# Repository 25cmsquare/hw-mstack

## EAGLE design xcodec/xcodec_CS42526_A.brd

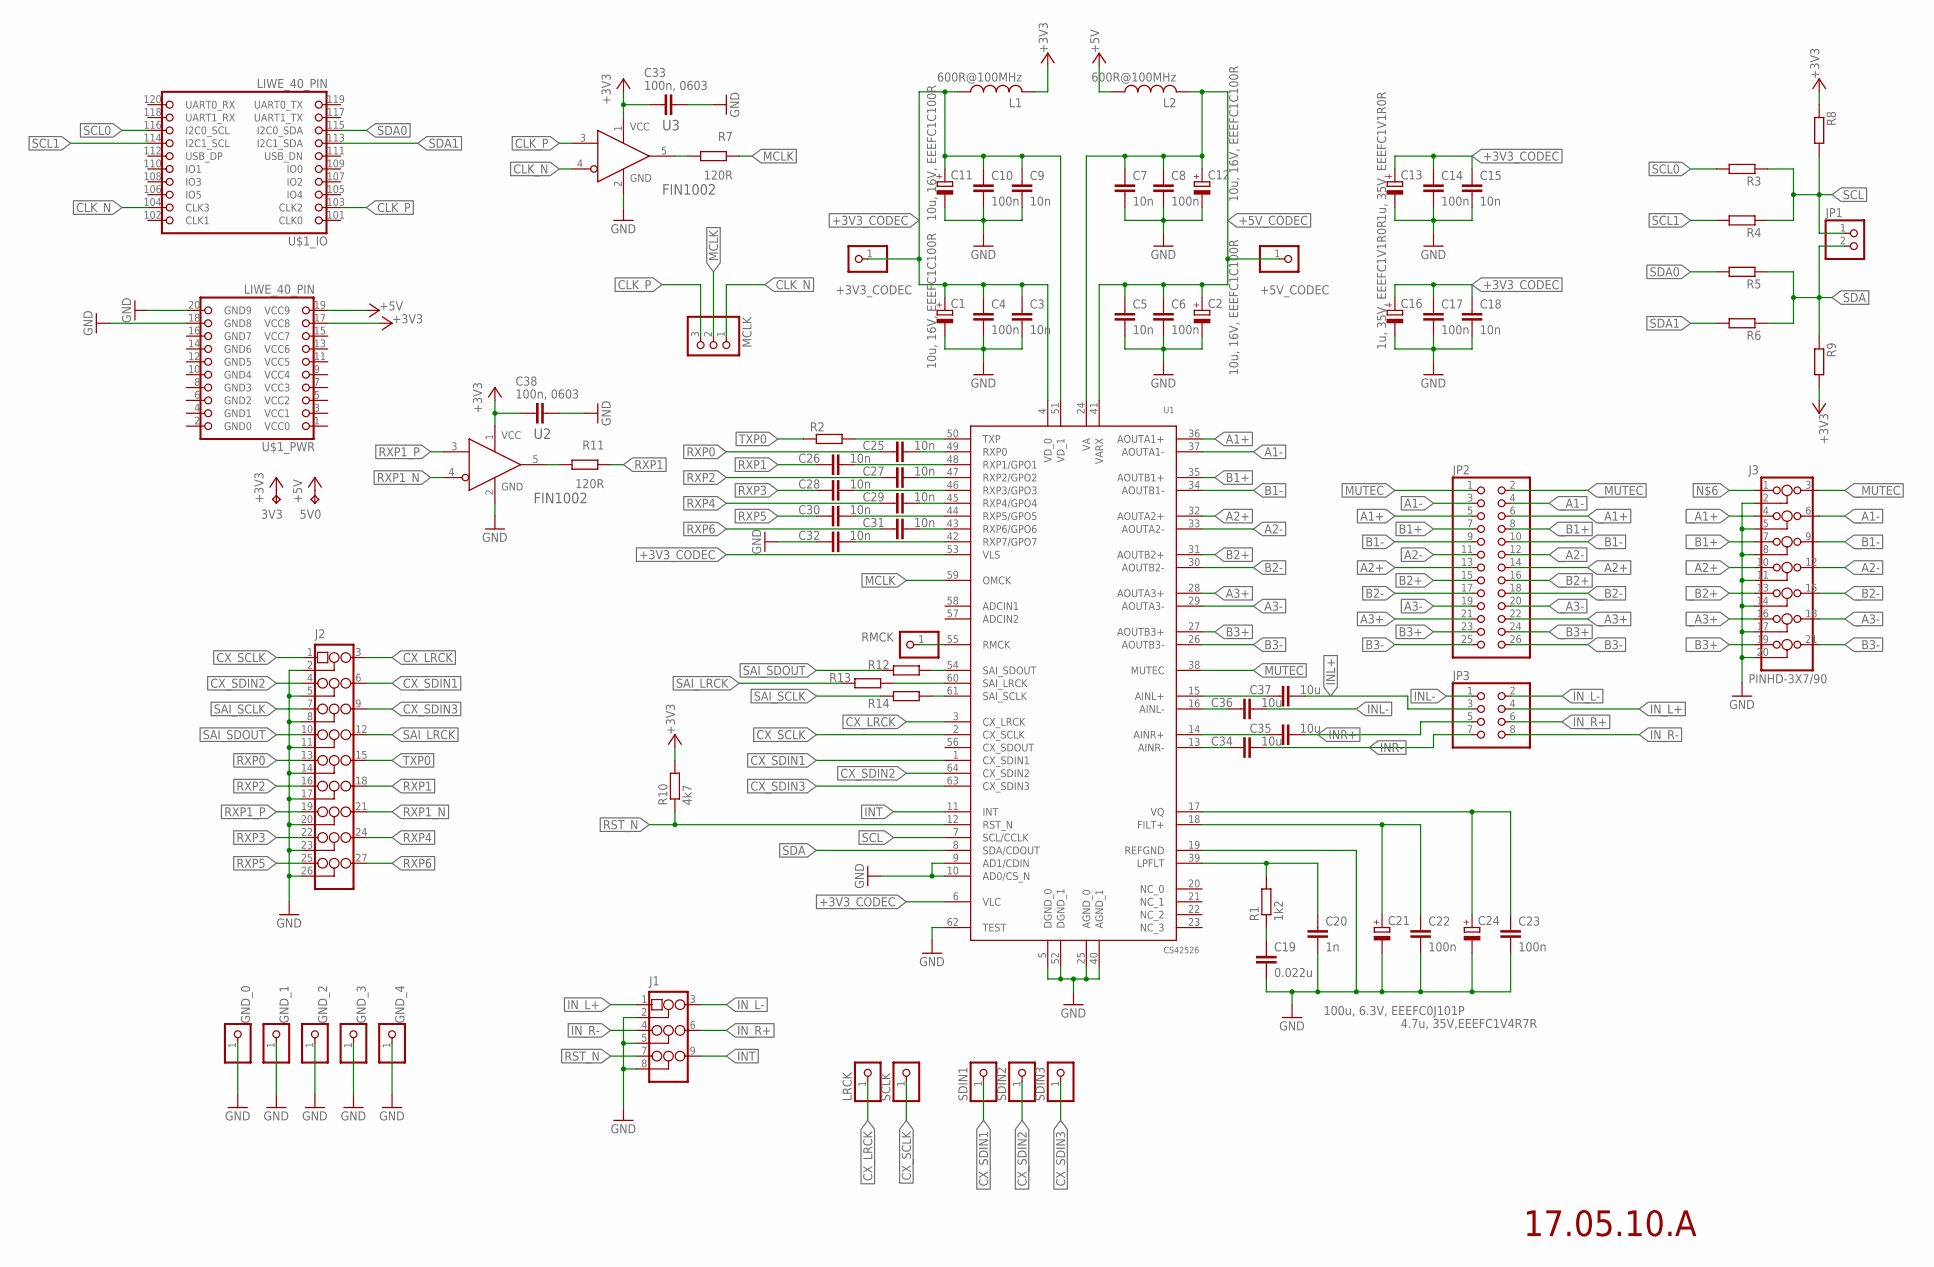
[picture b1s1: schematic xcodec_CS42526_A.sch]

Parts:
3V3, 5V0: TPTP14R; TP14R
+3V3_CODEC, +5V_CODEC: PINHD-1X1; 1X01
C1, C2, C11, C12: 10u, 16V, EEEFC1C100R; EEE-FC1V1R0AR
C3, C5, C7, C9, C15, C18, C25, C26, C27, C28, C29, C30, C31, C32: 10n; C0603K
C4, C6, C8, C10, C14, C17, C22, C23: 100n; C0603K
C13, C16: 1u, 35V, EEEFC1V1R0R; EEE-FC1V1R0AR
C19: 0.022u; C0603K
C20: 1n; C0603K
C21: 100u, 6.3V, EEEFC0J101P; EEE-FC1V220P
C24: 4.7u, 35V,EEEFC1V4R7R; EEE-FC1V1R0AR
C33, C38: 100n, 0603; C0603K
C34, C35, C36, C37: 10u; C0603K
GND_0, GND_1, GND_2, GND_3, GND_4: PINHD-1X1; 1X01
J1: PINHD-3X3/90; 3X03/90
J2: PINHD-3X9/90; 3X9/90
J3: PINHD-3X7/90; 3X07/90
JP1: PINHD-1X2; 1X02
JP2: PINHD-2X13; 2X13
JP3: PINHD-2X4; 2X04
L1, L2: 600R@100MHz; L0603
LRCK: PINHD-1X1; 1X01
MCLK: PINHD-1X3; 1X03
R1: 1k2; R0603
R2, R3, R4, R5, R6, R8, R9, R12, R13, R14: R-EU_R0603; R0603
R7, R11: 120R; R0603
R10: 4k7; R0603
RMCK: PINHD-1X1; 1X01
SCLK: PINHD-1X1; 1X01
SDIN1, SDIN2, SDIN3: PINHD-1X1; 1X01
U1: CS42526; LQFP_64
U2, U3: FIN1002; SOT95P280X140-5N
U$1: LIWE_40_PIN; LIWE_40_PIN_8X8

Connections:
+3V3: 3V3.TP, C33.2, C38.2, L1.2, R8.1, R9.2, R10.2, U2.1 (VCC), U3.1 (VCC), U$1.17 (VCC8)
+3V3_CODEC: +3V3_CODEC.1, C1.1 (+), C3.1, C4.1, C9.1, C10.1, C11.1 (+), C13.1 (+), C14.1, C15.1, C16.1 (+), C17.1, C18.1, L1.1, U1.4 (VD_0), U1.6 (VLC), U1.51 (VD_1), U1.53 (VLS)
+5V: 5V0.TP, L2.1, U$1.19 (VCC9)
+5V_CODEC: +5V_CODEC.1, C2.1 (+), C5.1, C6.1, C7.1, C8.1, C12.1 (+), L2.2, U1.24 (VA), U1.41 (VARX)
A1+: JP2.5, U1.36 (AOUTA1+)
A1-: JP2.3, U1.37 (AOUTA1-)
A2+: JP2.13, U1.32 (AOUTA2+)
A2-: JP2.11, U1.33 (AOUTA2-)
A3+: JP2.21, U1.28 (AOUTA3+)
A3-: JP2.19, U1.29 (AOUTA3-)
B1+: JP2.7, U1.35 (AOUTB1+)
B1-: JP2.9, U1.34 (AOUTB1-)
B2+: JP2.15, U1.31 (AOUTB2+)
B2-: JP2.17, U1.30 (AOUTB2-)
B3+: JP2.23, U1.27 (AOUTB3+)
B3-: JP2.25, U1.26 (AOUTB3-)
CLK_N: MCLK.1, U3.4 (RIN-), U$1.104 (CLK3)
CLK_P: MCLK.3, U3.3 (RIN+), U$1.103 (CLK2)
CX_LRCK: J2.3, LRCK.1, U1.3 (CX_LRCK)
CX_SCLK: J2.1, SCLK.1, U1.2 (CX_SCLK)
CX_SDIN1: J2.6, SDIN1.1, U1.1 (CX_SDIN1)
CX_SDIN2: J2.4, SDIN2.1, U1.64 (CX_SDIN2)
CX_SDIN3: J2.9, SDIN3.1, U1.63 (CX_SDIN3)
FILT+: C21.1 (+), C22.1, U1.18 (FILT+)
GND: C1.2 (-), C2.2 (-), C3.2, C4.2, C5.2, C6.2, C7.2, C8.2, C9.2, C10.2, C11.2 (-), C12.2 (-), C13.2 (-), C14.2, C15.2, C16.2 (-), C17.2, C18.2, C19.2, C20.2, C21.2 (-), C22.2, C23.2, C24.2 (-), C32.1, C33.1, C38.1, GND_0.1, GND_1.1, GND_2.1, GND_3.1, GND_4.1, J1.2, J1.5, J1.8, J2.2, J2.5, J2.8, J2.11, J2.14, J2.17, J2.20, J2.23, J2.26, J3.2, J3.5, J3.8, J3.11, J3.14, J3.17, J3.20, U1.5 (DGND_0), U1.9 (AD1/CDIN), U1.10 (AD0/CS_N), U1.19 (REFGND), U1.25 (AGND_0), U1.40 (AGND_1), U1.52 (DGND_1), U1.62 (TEST), U2.2 (GND), U3.2 (GND), U$1.18 (GND8), U$1.20 (GND9)
INL+: C37.2, JP3.3
INL-: C36.2, JP3.1
INR+: C35.2, JP3.5
INR-: C34.2, JP3.7
INT: J1.9, U1.11 (INT)
IN_L+: J1.1, JP3.4
IN_L-: J1.3, JP3.2
IN_R+: J1.6, JP3.6
IN_R-: J1.4, JP3.8
LPFLT: C20.1, R1.2, U1.39 (LPFLT)
MCLK: MCLK.2, R7.1, U1.59 (OMCK)
MUTEC: JP2.1, U1.38 (MUTEC)
unnamed: R12.1, U1.54 (SAI_SDOUT)
unnamed: R11.2, U2.5 (ROUT)
unnamed: C19.1, R1.1
unnamed: R13.1, U1.60 (SAI_LRCK)
unnamed: R14.1, U1.61 (SAI_SCLK)
unnamed: R7.2, U3.5 (ROUT)
unnamed: C37.1, U1.15 (AINL+)
unnamed: C36.1, U1.16 (AINL-)
unnamed: C35.1, U1.14 (AINR+)
unnamed: C34.1, U1.13 (AINR-)
RMCK: RMCK.1, U1.55 (RMCK)
RP0: C25.2, U1.49 (RXP0)
RP1: C26.2, U1.48 (RXP1/GPO1)
RP2: C27.2, U1.47 (RXP2/GPO2)
RP3: C28.2, U1.46 (RXP3/GPO3)
RP4: C29.2, U1.45 (RXP4/GPO4)
RP5: C30.2, U1.44 (RXP5/GPO5)
RP6: C31.2, U1.43 (RXP6/GPO6)
RP7: C32.2, U1.42 (RXP7/GPO7)
RST_N: J1.7, R10.1, U1.12 (RST_N)
RXP0: C25.1, J2.13
RXP1: C26.1, J2.18, R11.1
RXP1_N: J2.21, U2.4 (RIN-)
RXP1_P: J2.19, U2.3 (RIN+)
RXP2: C27.1, J2.16
RXP3: C28.1, J2.22
RXP4: C29.1, J2.24
RXP5: C30.1, J2.25
RXP6: C31.1, J2.27
SAI_LRCK: J2.12, R13.2
SAI_SCLK: J2.7, R14.2
SAI_SDOUT: J2.10, R12.2
SCL: JP1.1, R3.1, R4.1, R8.2, U1.7 (SCL/CCLK)
SCL0: R3.2, U$1.116 (I2C0_SCL)
SCL1: R4.2, U$1.114 (I2C1_SCL)
SDA: JP1.2, R5.1, R6.1, R9.1, U1.8 (SDA/CDOUT)
SDA0: R5.2, U$1.115 (I2C0_SDA)
SDA1: R6.2, U$1.113 (I2C1_SDA)
TP0: R2.2, U1.50 (TXP)
TXP0: J2.15, R2.1
VQ: C23.1, C24.1 (+), U1.17 (VQ)
_A1+: J3.4, JP2.6
_A1-: J3.6, JP2.4
_A2+: J3.10, JP2.14
_A2-: J3.12, JP2.12
_A3+: J3.16, JP2.22
_A3-: J3.18, JP2.20
_B1+: J3.7, JP2.8
_B1-: J3.9, JP2.10
_B2+: J3.13, JP2.16
_B2-: J3.15, JP2.18
_B3+: J3.19, JP2.24
_B3-: J3.21, JP2.26
_MUTEC: J3.3, JP2.2

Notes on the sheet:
17.05.10.A

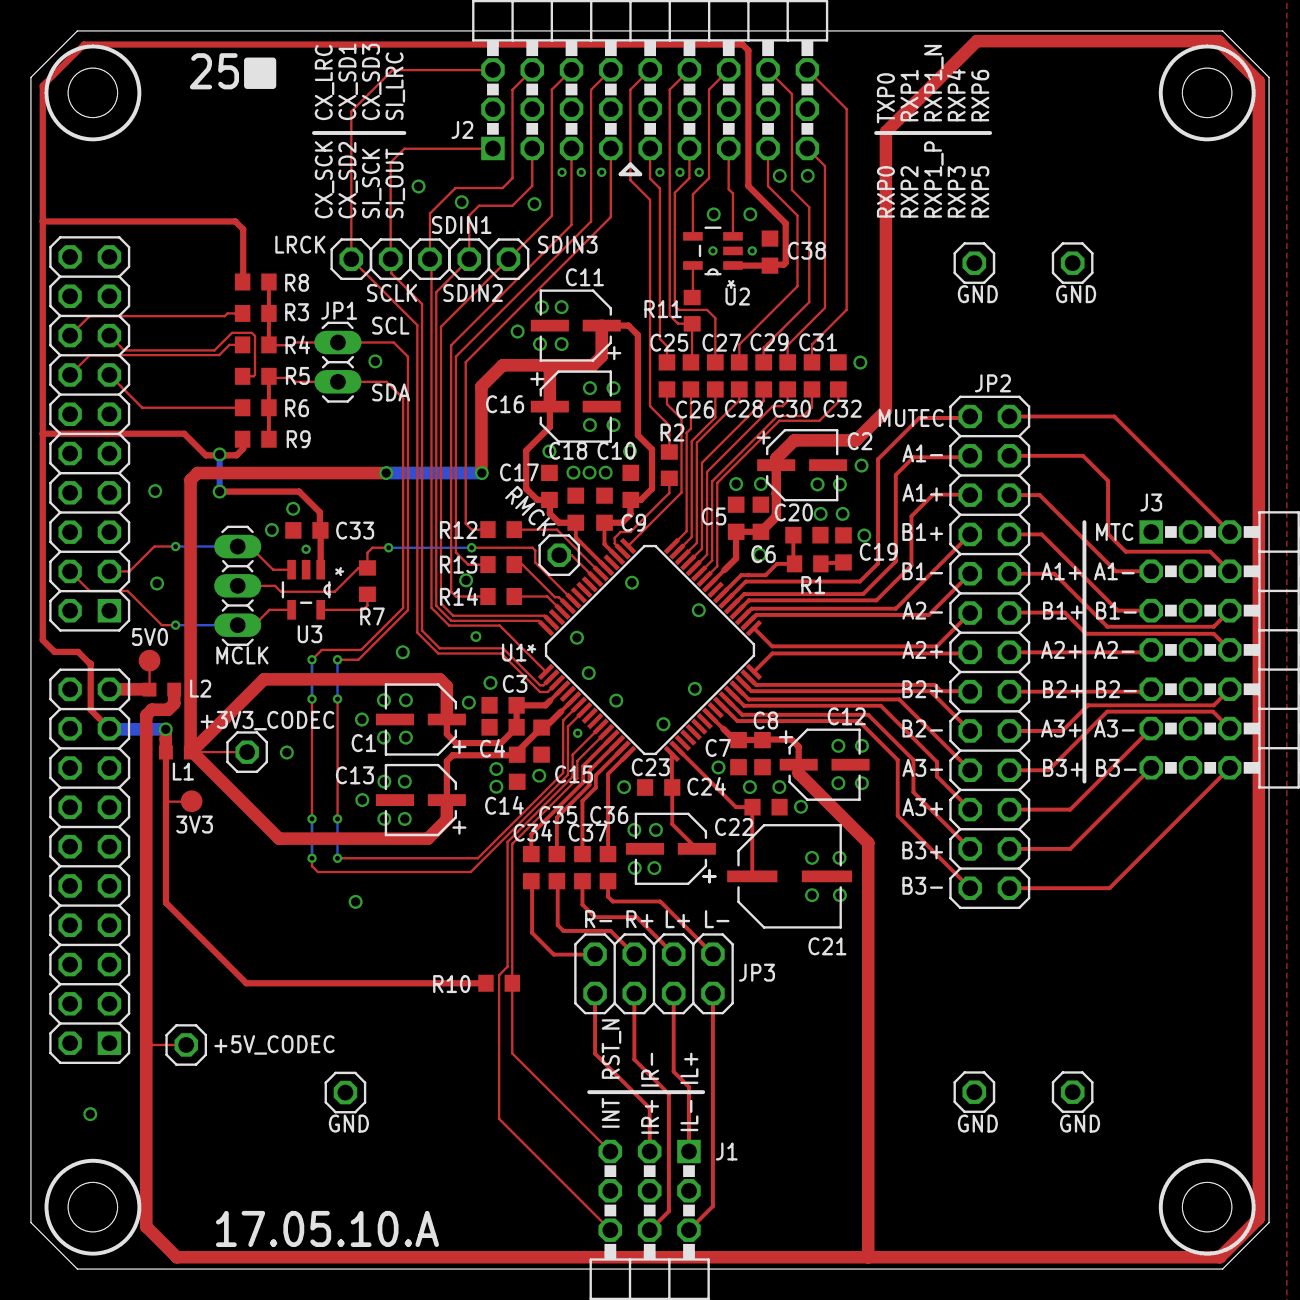
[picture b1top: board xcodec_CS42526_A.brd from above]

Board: 2 copper layers, 80.0 x 80.0 mm, 80 parts (0 on the bottom side), 91 nets.

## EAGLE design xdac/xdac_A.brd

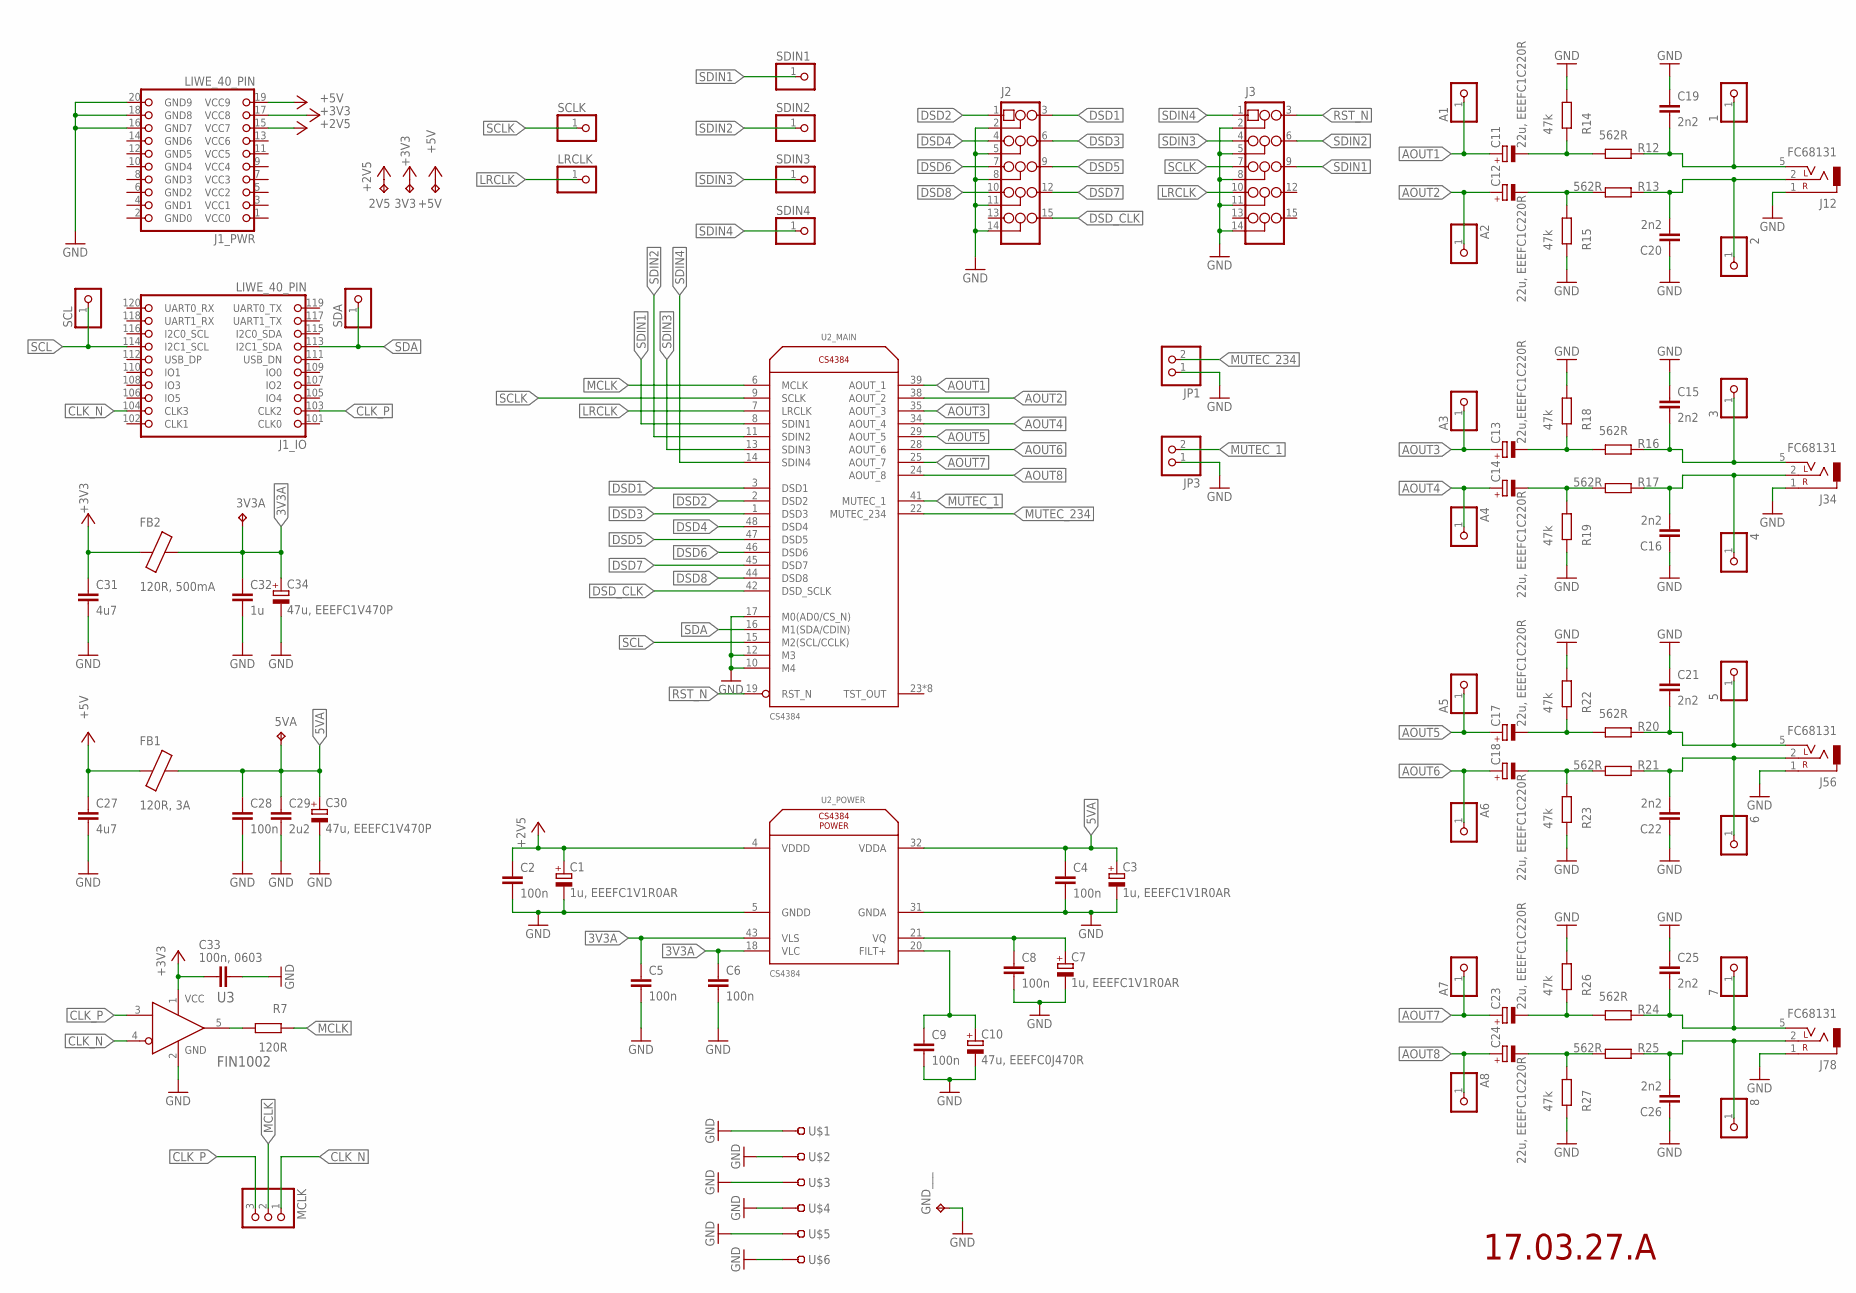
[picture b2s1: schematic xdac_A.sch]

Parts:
1, 2, 3, 4, 5, 6, 7, 8: PINHD-1X1; 1X01
2V5, 3V3, 3V3A, 5VA: TPTP14R; TP14R
+5V: TPTP14R; TP14R
A1, A2, A3, A4, A5, A6, A7, A8: PINHD-1X1; 1X01
C1, C3, C7: 1u, EEEFC1V1R0AR; EEE-FC1V1R0AR
C2, C4, C5, C8, C9: 100n; C0603
C6, C28: 100n; C0603K
C10: 47u, EEEFC0J470R; EEE-FC1C220R
C11, C12, C14, C17, C18, C23, C24: 22u, EEEFC1C220R; EEE-FC1C220R
C13: 22u,EEEFC1C220R; EEE-FC1C220R
C15, C16, C19, C20, C21, C22, C25, C26: 2n2; C0603
C27, C31: 4u7; C0603K
C29: 2u2; C0603K
C30, C34: 47u, EEEFC1V470P; EEE-FC1V470P
C32: 1u; C0603K
C33: 100n, 0603; C0603
FB1: 120R, 3A; L0603
FB2: 120R, 500mA; L0603
GND___: TPTP14R; TP14R
J1: LIWE_40_PIN; LIWE_40_PIN_8X8
J2, J3: PINHD-3X5/90; 3X05/90
J12, J34, J56, J78: FC68131
JP1, JP3: PINHD-1X2/90; 1X02/90
LRCLK: PINHD-1X1; 1X01
MCLK: PINHD-1X3; 1X03
R7: 120R; R0603
R12, R13, R16, R17, R20, R21, R24, R25: 562R; R0603
R14, R15, R18, R19, R22, R23, R26, R27: 47k; R0603
SCL: PINHD-1X1; 1X01
SCLK: PINHD-1X1; 1X01
SDA: PINHD-1X1; 1X01
SDIN1, SDIN2, SDIN3, SDIN4: PINHD-1X1; 1X01
U2: CS4384; LQFP_48
U3: FIN1002; SOT95P280X140-5N
U$1, U$2, U$3, U$4, U$5, U$6: TEST-22-MULTICOMP; TEST_1MM

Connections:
3V3A: 3V3A.TP, C5.1, C6.1, C32.1, C34.1 (+), FB2.1, U2.18 (VLC), U2.43 (VLS)
5VA: 5VA.TP, C3.1 (+), C4.1, C28.1, C29.1, C30.1 (+), FB1.1, U2.32 (VDDA)
+2V5: 2V5.TP, C1.1 (+), C2.1, J1.15 (VCC7), U2.4 (VDDD)
+3V3: 3V3.TP, C31.1, C33.2, FB2.2, J1.17 (VCC8), U3.1 (VCC)
+5V: +5V.TP, C27.1, FB1.2, J1.19 (VCC9)
AOUT1: A1.1, C11.1 (+), U2.39 (AOUT_1)
AOUT2: A2.1, C12.1 (+), U2.38 (AOUT_2)
AOUT2_: 2.1, C20.2, J12.2, R13.2
AOUT3: A3.1, C13.1 (+), U2.35 (AOUT_3)
AOUT3_: 3.1, C15.2, J34.5 (3), R16.2
AOUT4: A4.1, C14.1 (+), U2.34 (AOUT_4)
AOUT4_: 4.1, C16.2, J34.2, R17.2
AOUT5: A5.1, C17.1 (+), U2.29 (AOUT_5)
AOUT5_: 5.1, C21.2, J56.5 (3), R20.2
AOUT6: A6.1, C18.1 (+), U2.28 (AOUT_6)
AOUT6_: 6.1, C22.2, J56.2, R21.2
AOUT7: A7.1, C23.1 (+), U2.25 (AOUT_7)
AOUT7_: 7.1, C25.2, J78.5 (3), R24.2
AOUT8: A8.1, C24.1 (+), U2.24 (AOUT_8)
AOUT8_: 8.1, C26.2, J78.2, R25.2
AUOT1_: 1.1, C19.2, J12.5 (3), R12.2
CLK_N: J1.104 (CLK3), MCLK.1, U3.4 (RIN-)
CLK_P: J1.103 (CLK2), MCLK.3, U3.3 (RIN+)
DSD1: J2.3, U2.3 (DSD1)
DSD2: J2.1, U2.2 (DSD2)
DSD3: J2.6, U2.1 (DSD3)
DSD4: J2.4, U2.48 (DSD4)
DSD5: J2.9, U2.47 (DSD5)
DSD6: J2.7, U2.46 (DSD6)
DSD7: J2.12, U2.45 (DSD7)
DSD8: J2.10, U2.44 (DSD8)
DSD_CLK: J2.15, U2.42 (DSD_SCLK)
FILT+: C9.1, C10.1 (+), U2.20 (FILT+)
GND: C1.2 (-), C2.2, C3.2 (-), C4.2, C5.2, C6.2, C7.2 (-), C8.2, C9.2, C10.2 (-), C15.1, C16.1, C19.1, C20.1, C21.1, C22.1, C25.1, C26.1, C27.2, C28.2, C29.2, C30.2 (-), C31.2, C32.2, C33.1, C34.2 (-), GND___.TP, J1.16 (GND7), J1.18 (GND8), J1.20 (GND9), J2.2, J2.5, J2.8, J2.11, J2.14, J3.2, J3.5, J3.8, J3.11, J3.14, J12.1, J34.1, J56.1, J78.1, JP1.1, JP3.1, R14.2, R15.1, R18.2, R19.1, R22.2, R23.1, R26.2, R27.1, U2.5 (GNDD), U2.10 (M4), U2.12 (M3), U2.17 (M0(AD0/CS_N)), U2.31 (GNDA), U3.2 (GND), U$1.1, U$2.1, U$3.1, U$4.1, U$5.1, U$6.1
LRCLK: J3.10, LRCLK.1, U2.7 (LRCLK)
MCLK: MCLK.2, R7.1, U2.6 (MCLK)
MUTEC_1: JP3.2, U2.41 (MUTEC_1)
MUTEC_234: JP1.2, U2.22 (MUTEC_234)
unnamed: R7.2, U3.5 (ROUT)
unnamed: C11.2 (-), R12.1, R14.1
unnamed: C12.2 (-), R13.1, R15.2
unnamed: C13.2 (-), R16.1, R18.1
unnamed: C14.2 (-), R17.1, R19.2
unnamed: C17.2 (-), R20.1, R22.1
unnamed: C18.2 (-), R21.1, R23.2
unnamed: C23.2 (-), R24.1, R26.1
unnamed: C24.2 (-), R25.1, R27.2
RST_N: J3.3, U2.19 (RST_N)
SCL: J1.114 (I2C1_SCL), SCL.1, U2.15 (M2(SCL/CCLK))
SCLK: J3.7, SCLK.1, U2.9 (SCLK)
SDA: J1.113 (I2C1_SDA), SDA.1, U2.16 (M1(SDA/CDIN))
SDIN1: J3.9, SDIN1.1, U2.8 (SDIN1)
SDIN2: J3.6, SDIN2.1, U2.11 (SDIN2)
SDIN3: J3.4, SDIN3.1, U2.13 (SDIN3)
SDIN4: J3.1, SDIN4.1, U2.14 (SDIN4)
VQ: C7.1 (+), C8.1, U2.21 (VQ)

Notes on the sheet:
17.03.27.A

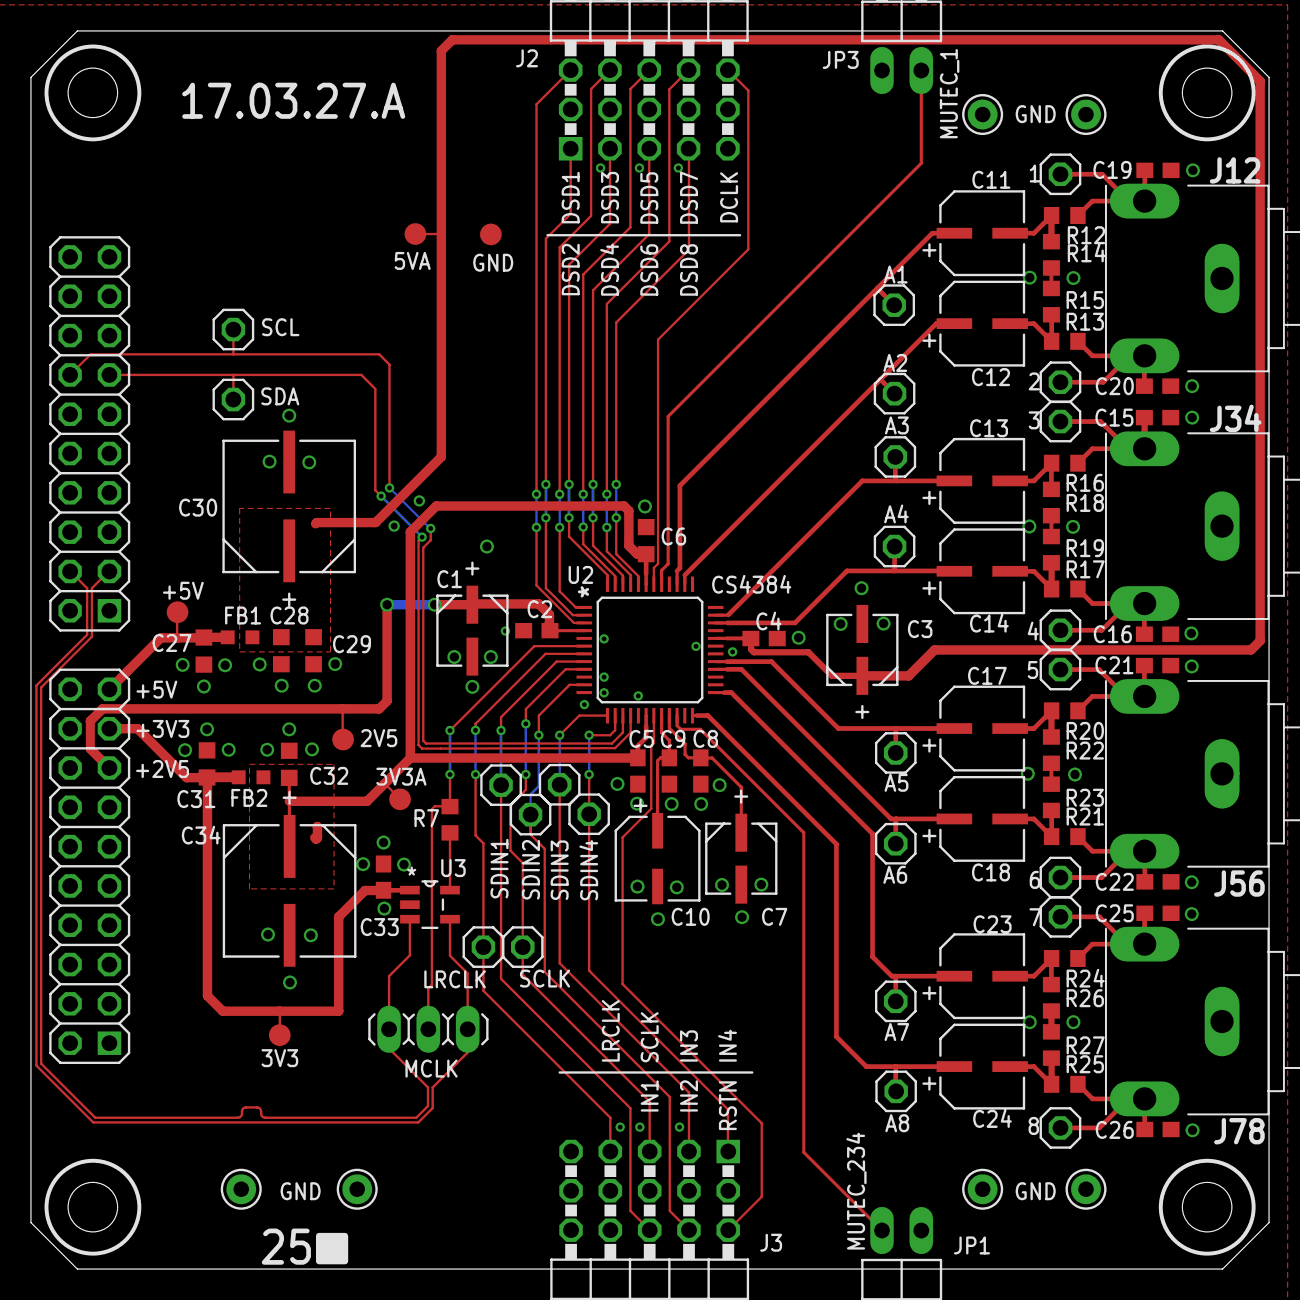
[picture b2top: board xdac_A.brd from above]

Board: 2 copper layers, 80.0 x 80.0 mm, 101 parts (0 on the bottom side), 56 nets.

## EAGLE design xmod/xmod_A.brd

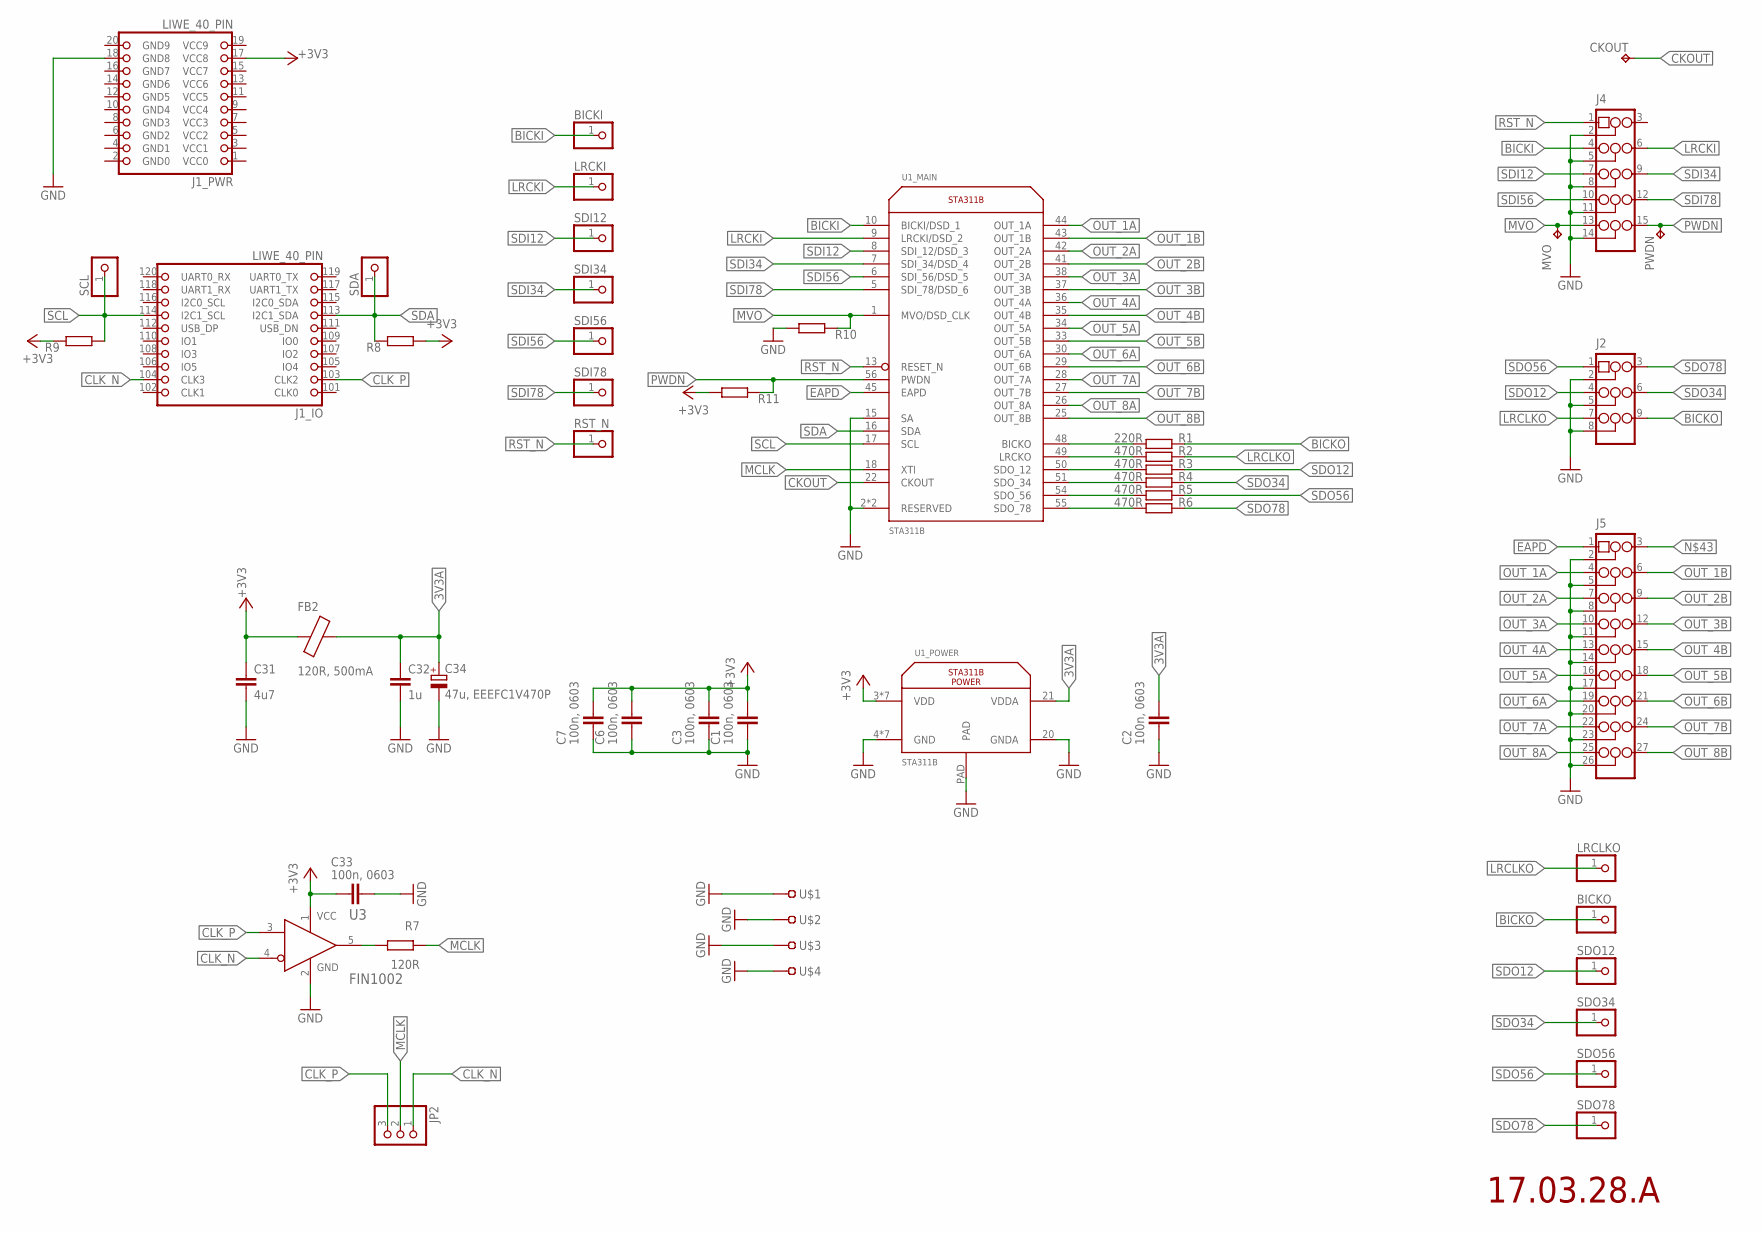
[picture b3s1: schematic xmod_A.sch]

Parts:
BICKI: PINHD-1X1; 1X01
BICKO: PINHD-1X1; 1X01
C1, C2, C3, C6, C7, C33: 100n, 0603; C0603
C31: 4u7; C0603K
C32: 1u; C0603K
C34: 47u, EEEFC1V470P; EEE-FC1V470P
CKOUT: TPTP14R; TP14R
FB2: 120R, 500mA; L0603
J1: LIWE_40_PIN; LIWE_40_PIN_8X8
J2: PINHD-3X3/90; 3X03/90
J4: PINHD-3X5/90; 3X05/90
J5: PINHD-3X9/90; 3X9/90
JP2: PINHD-1X3; 1X03
LRCKI: PINHD-1X1; 1X01
LRCLKO: PINHD-1X1; 1X01
MVO: TPTP14R; TP14R
PWDN: TPTP14R; TP14R
R1: 220R; R0603
R2, R3, R4, R5, R6: 470R; R0603
R7: 120R; R0603
R8, R9, R10, R11: R-EU_R0603; R0603
RST_N: PINHD-1X1; 1X01
SCL: PINHD-1X1; 1X01
SDA: PINHD-1X1; 1X01
SDI12, SDI34, SDI56, SDI78: PINHD-1X1; 1X01
SDO12, SDO34, SDO56, SDO78: PINHD-1X1; 1X01
U1: STA311B; VFQFPN_56_8X8
U3: FIN1002; SOT95P280X140-5N
U$1, U$2, U$3, U$4: TEST-22-MULTICOMP; TEST_1MM

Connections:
3V3A: C2.1, C32.1, C34.1 (+), FB2.1, U1.21 (VDDA)
+3V3: C1.1, C3.1, C6.1, C7.1, C31.1, C33.2, FB2.2, J1.17 (VCC8), R8.1, R9.2, R11.2, U1.3 (VDD), U1.11 (VDD), U1.24 (VDD), U1.31 (VDD), U1.39 (VDD), U1.46 (VDD), U1.52 (VDD), U3.1 (VCC)
BICKI: BICKI.1, J4.4, U1.10 (BICKI/DSD_1)
BICKO: BICKO.1, J2.9, R1.2
CKOUT: CKOUT.TP, U1.22 (CKOUT)
CLK_N: J1.104 (CLK3), JP2.1, U3.4 (RIN-)
CLK_P: J1.103 (CLK2), JP2.3, U3.3 (RIN+)
EAPD: J5.1, U1.45 (EAPD)
GND: C1.2, C2.2, C3.2, C6.2, C7.2, C31.2, C32.2, C33.1, C34.2 (-), J1.18 (GND8), J2.2, J2.5, J2.8, J4.2, J4.5, J4.8, J4.11, J4.14, J5.2, J5.5, J5.8, J5.11, J5.14, J5.17, J5.20, J5.23, J5.26, R10.2, U1.2 (RESERVED), U1.4 (GND), U1.12 (GND), U1.14 (RESERVED), U1.15 (SA), U1.20 (GNDA), U1.23 (GND), U1.32 (GND), U1.40 (GND), U1.47 (GND), U1.53 (GND), U1.PAD, U3.2 (GND), U$1.1, U$2.1, U$3.1, U$4.1
LRCKI: J4.6, LRCKI.1, U1.9 (LRCKI/DSD_2)
LRCLKO: J2.7, LRCLKO.1, R2.2
MCLK: JP2.2, R7.1, U1.18 (XTI)
MVO: J4.13, MVO.TP, R10.1, U1.1 (MVO/DSD_CLK)
unnamed: R1.1, U1.48 (BICKO)
unnamed: R2.1, U1.49 (LRCKO)
unnamed: R3.1, U1.50 (SDO_12)
unnamed: R4.1, U1.51 (SDO_34)
unnamed: R5.1, U1.54 (SDO_56)
unnamed: R6.1, U1.55 (SDO_78)
unnamed: R7.2, U3.5 (ROUT)
OUT_1A: J5.4, U1.44 (OUT_1A)
OUT_1B: J5.6, U1.43 (OUT_1B)
OUT_2A: J5.7, U1.42 (OUT_2A)
OUT_2B: J5.9, U1.41 (OUT_2B)
OUT_3A: J5.10, U1.38 (OUT_3A)
OUT_3B: J5.12, U1.37 (OUT_3B)
OUT_4A: J5.13, U1.36 (OUT_4A)
OUT_4B: J5.15, U1.35 (OUT_4B)
OUT_5A: J5.16, U1.34 (OUT_5A)
OUT_5B: J5.18, U1.33 (OUT_5B)
OUT_6A: J5.19, U1.30 (OUT_6A)
OUT_6B: J5.21, U1.29 (OUT_6B)
OUT_7A: J5.22, U1.28 (OUT_7A)
OUT_7B: J5.24, U1.27 (OUT_7B)
OUT_8A: J5.25, U1.26 (OUT_8A)
OUT_8B: J5.27, U1.25 (OUT_8B)
PWDN: J4.15, PWDN.TP, R11.1, U1.56 (PWDN)
RST_N: J4.1, RST_N.1, U1.13 (RESET_N)
SCL: J1.114 (I2C1_SCL), R9.1, SCL.1, U1.17 (SCL)
SDA: J1.113 (I2C1_SDA), R8.2, SDA.1, U1.16 (SDA)
SDI12: J4.7, SDI12.1, U1.8 (SDI_12/DSD_3)
SDI34: J4.9, SDI34.1, U1.7 (SDI_34/DSD_4)
SDI56: J4.10, SDI56.1, U1.6 (SDI_56/DSD_5)
SDI78: J4.12, SDI78.1, U1.5 (SDI_78/DSD_6)
SDO12: J2.4, R3.2, SDO12.1
SDO34: J2.6, R4.2, SDO34.1
SDO56: J2.1, R5.2, SDO56.1
SDO78: J2.3, R6.2, SDO78.1

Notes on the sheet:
17.03.28.A

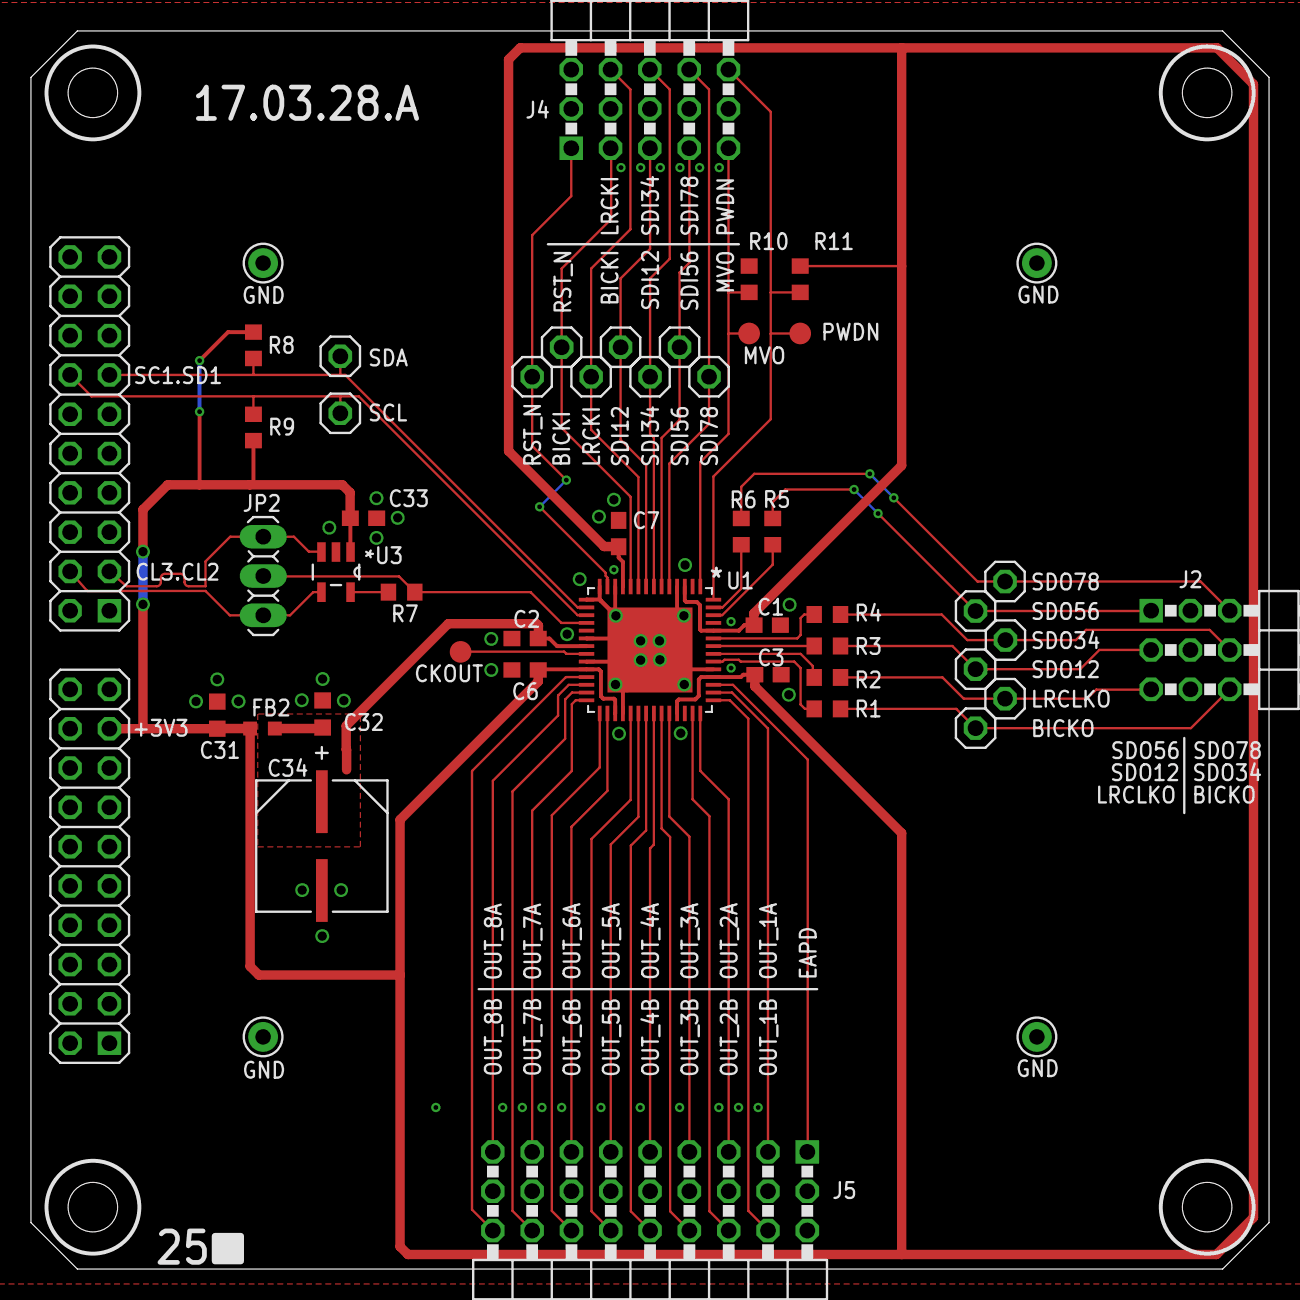
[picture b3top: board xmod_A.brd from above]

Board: 2 copper layers, 80.0 x 80.0 mm, 50 parts (0 on the bottom side), 48 nets.

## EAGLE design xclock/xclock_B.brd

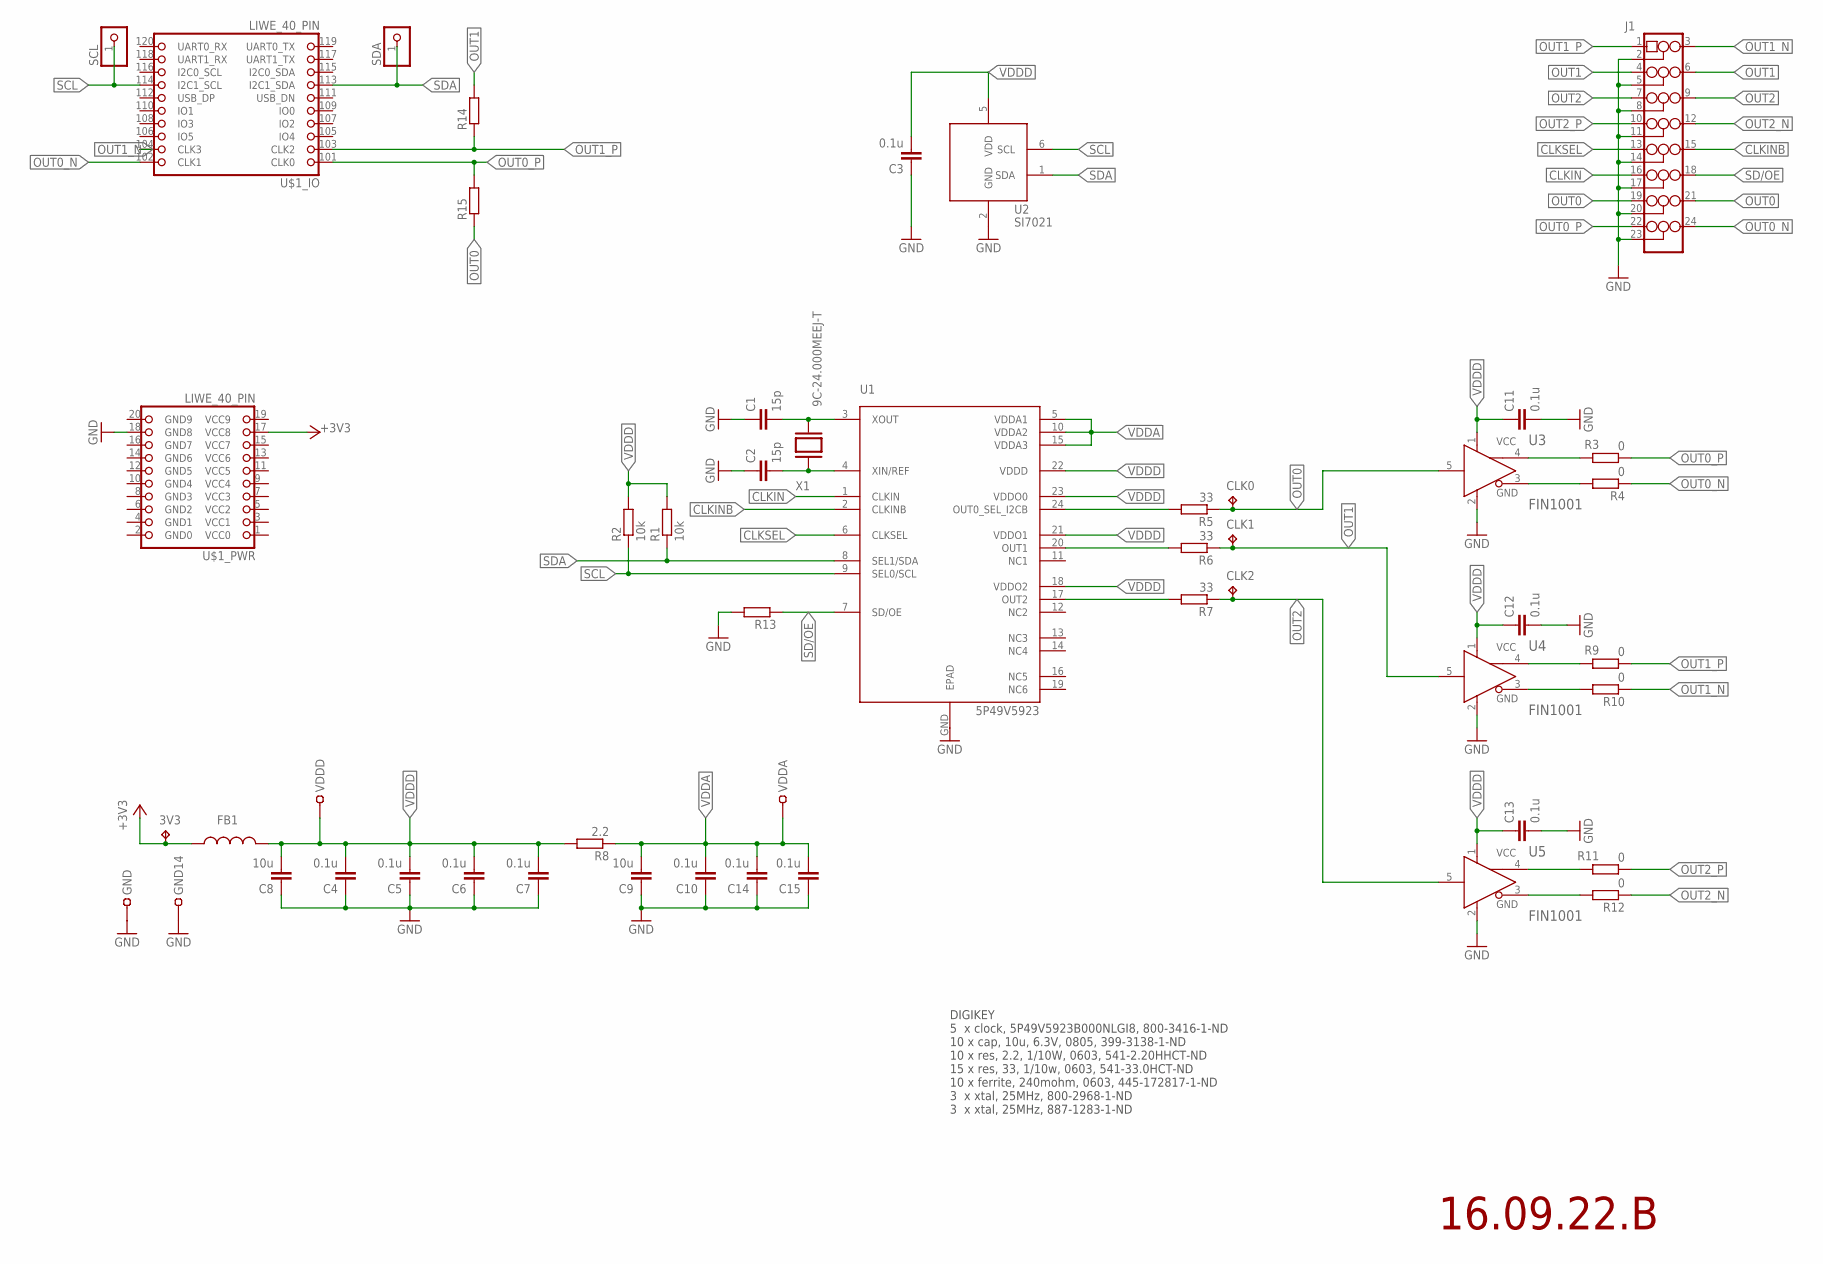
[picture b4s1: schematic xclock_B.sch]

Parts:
3V3: TPB1,27; B1,27
C1, C2: 15p; C0603
C3, C4, C5, C6, C7, C10, C11, C12, C13, C14, C15: 0.1u; C0603
C8, C9: 10u; C0805
CLK0, CLK1, CLK2: TPB1,27; B1,27
FB1: L0603(1608); L0603
GND, GND14: TEST-22-MULTICOMP; TEST_1MM
J1: PINHD-3X8/90; 3X08/90
R1, R2: 10k; R0603
R3, R4, R9, R10, R11, R12: 0; R0603
R5, R6, R7: 33; R0603
R8: 2.2; R0603
R13, R14, R15: R-EU_R0603; R0603
SCL: PINHD-1X1; 1X01
SDA: PINHD-1X1; 1X01
U1: 5P49V5923; VFQFPN_24_4X4
U2: SI7021
U3, U4, U5: FIN1001; SOT95P280X140-5N
U$1: LIWE_40_PIN; LIWE_40_PIN_8X8
VDDA: TEST-22-MULTICOMP; TEST_1MM
VDDD: TEST-22-MULTICOMP; TEST_1MM
X1: 9C-24.000MEEJ-T; TXC_SMD_HC-49S

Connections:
+3V3: 3V3.TP, FB1.1, U$1.17 (VCC8)
CLKIN: J1.16, U1.1 (CLKIN)
CLKINB: J1.15, U1.2 (CLKINB)
CLKSEL: J1.13, U1.6 (CLKSEL)
GND: C1.1, C2.1, C3.1, C4.1, C5.1, C6.1, C7.1, C8.1, C9.1, C10.1, C11.2, C12.2, C13.2, C14.1, C15.1, GND.1, GND14.1, J1.2, J1.5, J1.8, J1.11, J1.14, J1.17, J1.20, J1.23, R13.2, U1.GND (EPAD), U2.2 (GND), U3.2 (GND), U4.2 (GND), U5.2 (GND), U$1.18 (GND8)
OUT0: CLK0.TP, J1.19, J1.21, R5.1, R15.1, U3.5 (RIN)
OUT0_: R5.2, U1.24 (OUT0_SEL_I2CB)
OUT0_N: J1.24, R4.1, U$1.102 (CLK1)
OUT0_N_: R4.2, U3.3 (ROUT-)
OUT0_P: J1.22, R3.1, R15.2, U$1.101 (CLK0)
OUT0_P_: R3.2, U3.4 (ROUT+)
OUT1: CLK1.TP, J1.4, J1.6, R6.1, R14.2, U4.5 (RIN)
OUT1_: R6.2, U1.20 (OUT1)
OUT1_N: J1.3, R10.1, U$1.104 (CLK3)
OUT1_N_: R10.2, U4.3 (ROUT-)
OUT1_P: J1.1, R9.1, R14.1, U$1.103 (CLK2)
OUT1_P_: R9.2, U4.4 (ROUT+)
OUT2: CLK2.TP, J1.7, J1.9, R7.1, U5.5 (RIN)
OUT2_: R7.2, U1.17 (OUT2)
OUT2_N: J1.12, R12.1
OUT2_N_: R12.2, U5.3 (ROUT-)
OUT2_P: J1.10, R11.1
OUT2_P_: R11.2, U5.4 (ROUT+)
SCL: R2.1, SCL.1, U1.9 (SEL0/SCL), U2.6 (SCL), U$1.114 (I2C1_SCL)
SD/OE: J1.18, R13.1, U1.7 (SD/OE)
SDA: R1.1, SDA.1, U1.8 (SEL1/SDA), U2.1 (SDA), U$1.113 (I2C1_SDA)
VDDA: C9.2, C10.2, C14.2, C15.2, R8.1, U1.5 (VDDA1), U1.10 (VDDA2), U1.15 (VDDA3), VDDA.1
VDDD: C3.2, C4.2, C5.2, C6.2, C7.2, C8.2, C11.1, C12.1, C13.1, FB1.2, R1.2, R2.2, R8.2, U1.18 (VDDO2), U1.21 (VDDO1), U1.22 (VDDD), U1.23 (VDDO0), U2.5 (VDD), U3.1 (VCC), U4.1 (VCC), U5.1 (VCC), VDDD.1
XIN: C2.2, U1.4 (XIN/REF), X1.1
XOUT: C1.2, U1.3 (XOUT), X1.2

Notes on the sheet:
16.09.22.B
DIGIKEY 5 x clock, 5P49V5923B000NLGI8, 800-3416-1-ND 10 x cap, 10u, 6.3V, 0805, 399-3138-1-ND 10 x res, 2.2, 1/10W, 0603, 541-2.20HHCT-ND 15 x res, 33, 1/10w, 0603, 541-33.0HCT-ND 10 x ferrite, 240mohm, 0603, 445-172817-1-ND 3 x xtal, 25MHz, 800-2968-1-ND 3 x xtal, 25MHz, 887-1283-1-ND
